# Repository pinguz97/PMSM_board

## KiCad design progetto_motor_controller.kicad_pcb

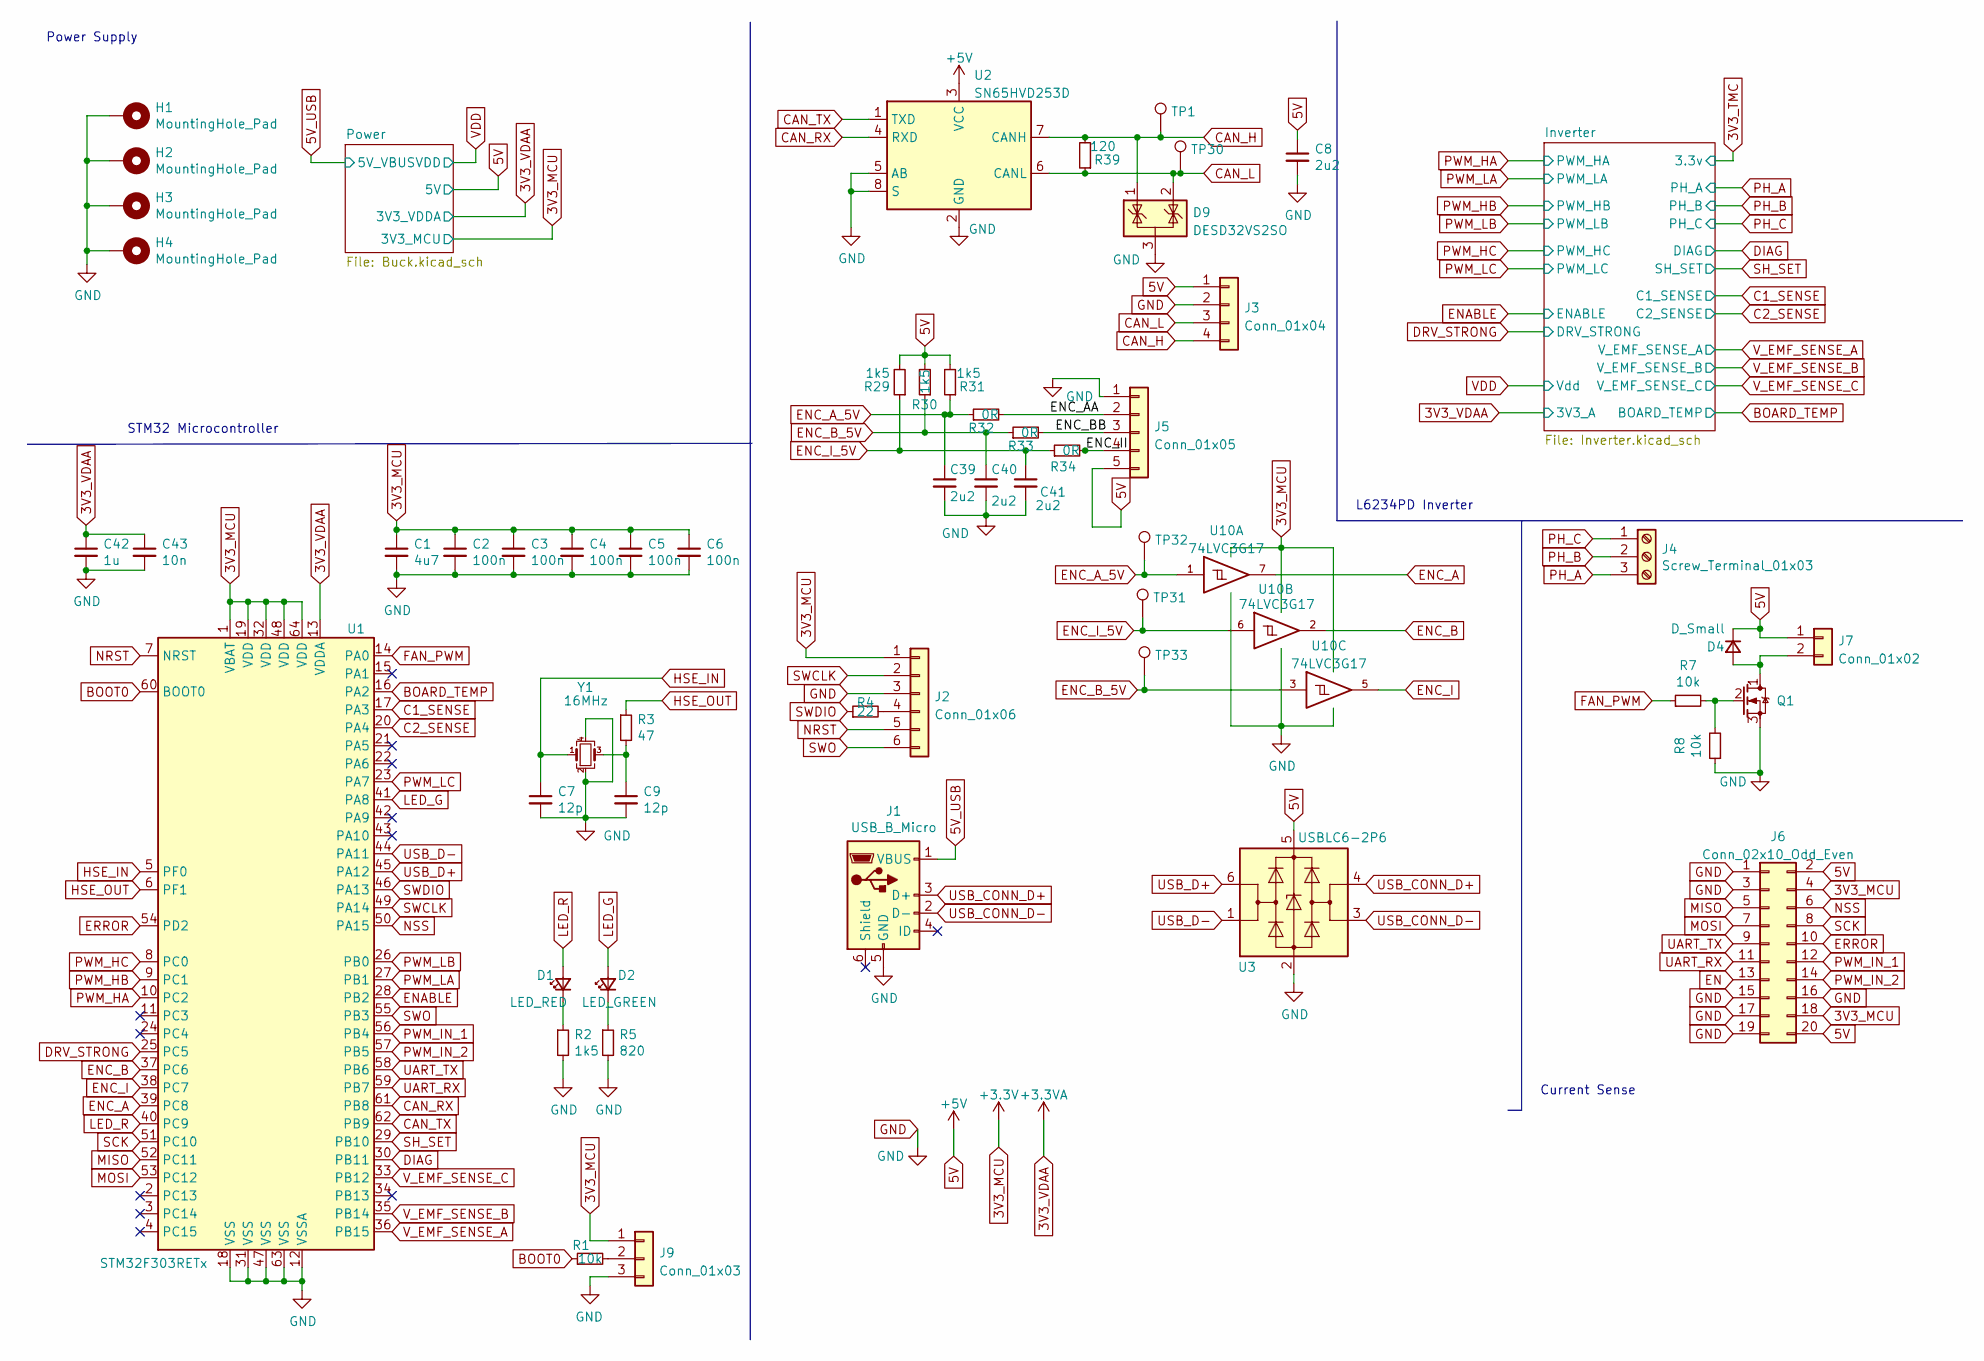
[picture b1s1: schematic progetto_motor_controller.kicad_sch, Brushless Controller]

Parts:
C1: 4u7; C_0603_1608Metric; Part CL10A475KP8NNNC
C2, C3, C4, C5, C6: 100n; C_0402_1005Metric; Part CL05B104KA5NNNC
C7, C9: 12p; C_0402_1005Metric; Part CL05C100JB5NNNC CL05C120JB5NNNC
C8, C39, C40, C41: 2u2; C_0603_1608Metric; Part CL10A225KO8NNNC
C42: 1u; C_0603_1608Metric; Part CL10B105KA8NNNC
C43: 10n; C_0402_1005Metric; Part CL05B103KB5NNNC
D1: LED_RED; LED_0603_1608Metric; Part B1931URO-20D000114U1930
D2: LED_GREEN; LED_0603_1608Metric; Part B19Y1NG--20C000113U1930
D4: D_Small; D_SOD-323; Part 1N4148WS
D9: DESD32VS2SO; SOT-23; Part DESD32VS2SO-7
H1, H2, H3, H4: MountingHole_Pad; MountingHole_3.2mm_M3_Pad_Via
J1: USB_B_Micro; USB_Micro-B_Amphenol_10118194_Horizontal
J2: Conn_01x06; JST_GH_SM06B-GHS-TB_06x1.25mm_Angled
J3: Conn_01x04; JST_GH_SM04B-GHS-TB_04x1.25mm_Angled
J4: Screw_Terminal_01x03; TerminalBlock_Phoenix_PT-1,5-3-5.0-H_1x03_P5.00mm_Horizontal
J5: Conn_01x05; JST_GH_SM05B-GHS-TB_05x1.25mm_Angled
J6: Conn_02x10_Odd_Even; JST_SHD_SM20B
J7: Conn_01x02; JST_GH_SM02B-GHS-TB_02x1.25mm_Angled
J9: Conn_01x03; PinHeader_1x03_P2.54mm_Vertical
Q1: DMG3402L-7; SOT-23; Part DMG3402L-7
R1, R7, R8: 10k; R_0603_1608Metric; Part AC0603FR-0710KL
R2, R29, R30, R31: 1k5; R_0603_1608Metric; Part AC0603JR-071K5L
R3: 47; R_0402_1005Metric
R4: 22; R_0603_1608Metric
R5: 820; R_0603_1608Metric
R32, R33, R34: 0R; R_0603_1608Metric
R39: 120; R_1210_3225Metric; Part RC1210JR-07120RL
TP1, TP30, TP31, TP32, TP33: Testpoint; TestPoint_1.0mm
U1: STM32F303RETx; LQFP-64_10x10mm_P0.5mm; Part STM32F303RETx --------
U2: SN65HVD253D; SOIC-8_3.9x4.9mm_P1.27mm; Part SN65HVD253D
U3: USBLC6-2P6; SOT-23-6; Part CM1231-02SO
U10: 74LVC3G17; VSSOP-8_2.3x2mm_P0.5mm; Part 74LVC3G34DC,125
Y1: 16MHz; Crystal_SMD_3225-4Pin_3.2x2.5mm; Part ABM8-16.000MHZ-10-1-U-T

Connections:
3V3_MCU: C1.1, C2.1, C3.1, C4.1, C5.1, C6.1, J2.1, J6.4, J6.18, J9.1, U1.1 (VBAT), U1.19 (VDD), U1.32 (VDD), U1.48 (VDD), U1.64 (VDD), U10.8 (VCC); also elsewhere on the board
3V3_VDAA: C42.1, C43.1, U1.13 (VDDA); also elsewhere on the board
5V: C8.1, D4.1 (K), J3.1, J5.5, J6.2, J6.20, J7.1, R29.2, R30.2, R31.2, U2.3 (VCC), U3.5 (VBUS); also elsewhere on the board
5V_USB: J1.1 (VBUS); also elsewhere on the board
/ENC_AA: J5.2, R32.2
/ENC_BB: J5.3, R33.2
/ENC_II: J5.4, R34.2
BOARD_TEMP: U1.16 (PA2); also elsewhere on the board
BOOT0: R1.1, U1.60 (BOOT0)
C1_SENSE: U1.17 (PA3); also elsewhere on the board
C2_SENSE: U1.20 (PA4); also elsewhere on the board
CAN_H: D9.1 (K), J3.4, R39.2, TP1.1, U2.7 (CANH)
CAN_L: D9.2 (K), J3.3, R39.1, TP30.1, U2.6 (CANL)
CAN_RX: U1.61 (PB8), U2.4 (RXD)
CAN_TX: U1.62 (PB9), U2.1 (TXD)
DIAG: U1.30 (PB11); also elsewhere on the board
DRV_STRONG: U1.25 (PC5); also elsewhere on the board
EN: J6.13
ENABLE: U1.28 (PB2); also elsewhere on the board
ENC_A: U1.39 (PC8), U10.7
ENC_A_5V: C39.1, R31.1, R32.1, TP32.1, U10.1
ENC_B: U1.37 (PC6), U10.2
ENC_B_5V: C40.1, R30.1, R33.1, TP33.1, U10.3
ENC_I: U1.38 (PC7), U10.5
ENC_I_5V: C41.1, R29.1, R34.1, TP31.1, U10.6
ERROR: J6.10, U1.54 (PD2)
FAN_PWM: R7.1, U1.14 (PA0)
GND: C1.2, C2.2, C3.2, C4.2, C5.2, C6.2, C7.2, C8.2, C9.2, C39.2, C40.2, C41.2, C42.2, C43.2, D9.3 (A), H1.1, H2.1, H3.1, H4.1, J1.5 (GND), J2.3, J3.2, J5.1, J6.1, J6.3, J6.15, J6.16, J6.17, J6.19, J9.3, Q1.3 (S), R2.2, R5.2, R8.1, U1.12 (VSSA), U1.18 (VSS), U1.31 (VSS), U1.47 (VSS), U1.63 (VSS), U2.2 (GND), U2.5 (AB), U2.8 (S), U3.2 (GND), U10.4 (GND), Y1.2, Y1.4; also elsewhere on the board
HSE_IN: C7.1, U1.5 (PF0), Y1.1
HSE_OUT: R3.1, U1.6 (PF1)
LED_G: D2.2 (A), U1.41 (PA8)
LED_R: D1.2 (A), U1.40 (PC9)
MISO: J6.5, U1.52 (PC11)
MOSI: J6.7, U1.53 (PC12)
NRST: J2.5, U1.7 (NRST)
NSS: J6.6, U1.50 (PA15)
unnamed: C9.1, R3.2, Y1.3
unnamed: D1.1 (K), R2.1
unnamed: D2.1 (K), R5.1
unnamed: D4.2 (A), J7.2, Q1.1 (D)
unnamed: J2.4, R4.2
unnamed: J9.2, R1.2
unnamed: Q1.2 (G), R7.2, R8.2
PH_A: J4.3; also elsewhere on the board
PH_B: J4.2; also elsewhere on the board
PH_C: J4.1; also elsewhere on the board
PWM_HA: U1.10 (PC2); also elsewhere on the board
PWM_HB: U1.9 (PC1); also elsewhere on the board
PWM_HC: U1.8 (PC0); also elsewhere on the board
PWM_IN_1: J6.12, U1.56 (PB4)
PWM_IN_2: J6.14, U1.57 (PB5)
PWM_LA: U1.27 (PB1); also elsewhere on the board
PWM_LB: U1.26 (PB0); also elsewhere on the board
PWM_LC: U1.23 (PA7); also elsewhere on the board
SCK: J6.8, U1.51 (PC10)
SH_SET: U1.29 (PB10); also elsewhere on the board
SWCLK: J2.2, U1.49 (PA14)
SWDIO: R4.1, U1.46 (PA13)
SWO: J2.6, U1.55 (PB3)
UART_RX: J6.11, U1.59 (PB7)
UART_TX: J6.9, U1.58 (PB6)
USB_CONN_D+: J1.3 (D+), U3.4 (I/O2)
USB_CONN_D-: J1.2 (D-), U3.3 (I/O2)
USB_D+: U1.45 (PA12), U3.6 (I/O1)
USB_D-: U1.44 (PA11), U3.1 (I/O1)
V_EMF_SENSE_A: U1.36 (PB15); also elsewhere on the board
V_EMF_SENSE_B: U1.35 (PB14); also elsewhere on the board
V_EMF_SENSE_C: U1.33 (PB12); also elsewhere on the board

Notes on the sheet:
STM32 Microcontroller
Current Sense
Power Supply
L6234PD Inverter

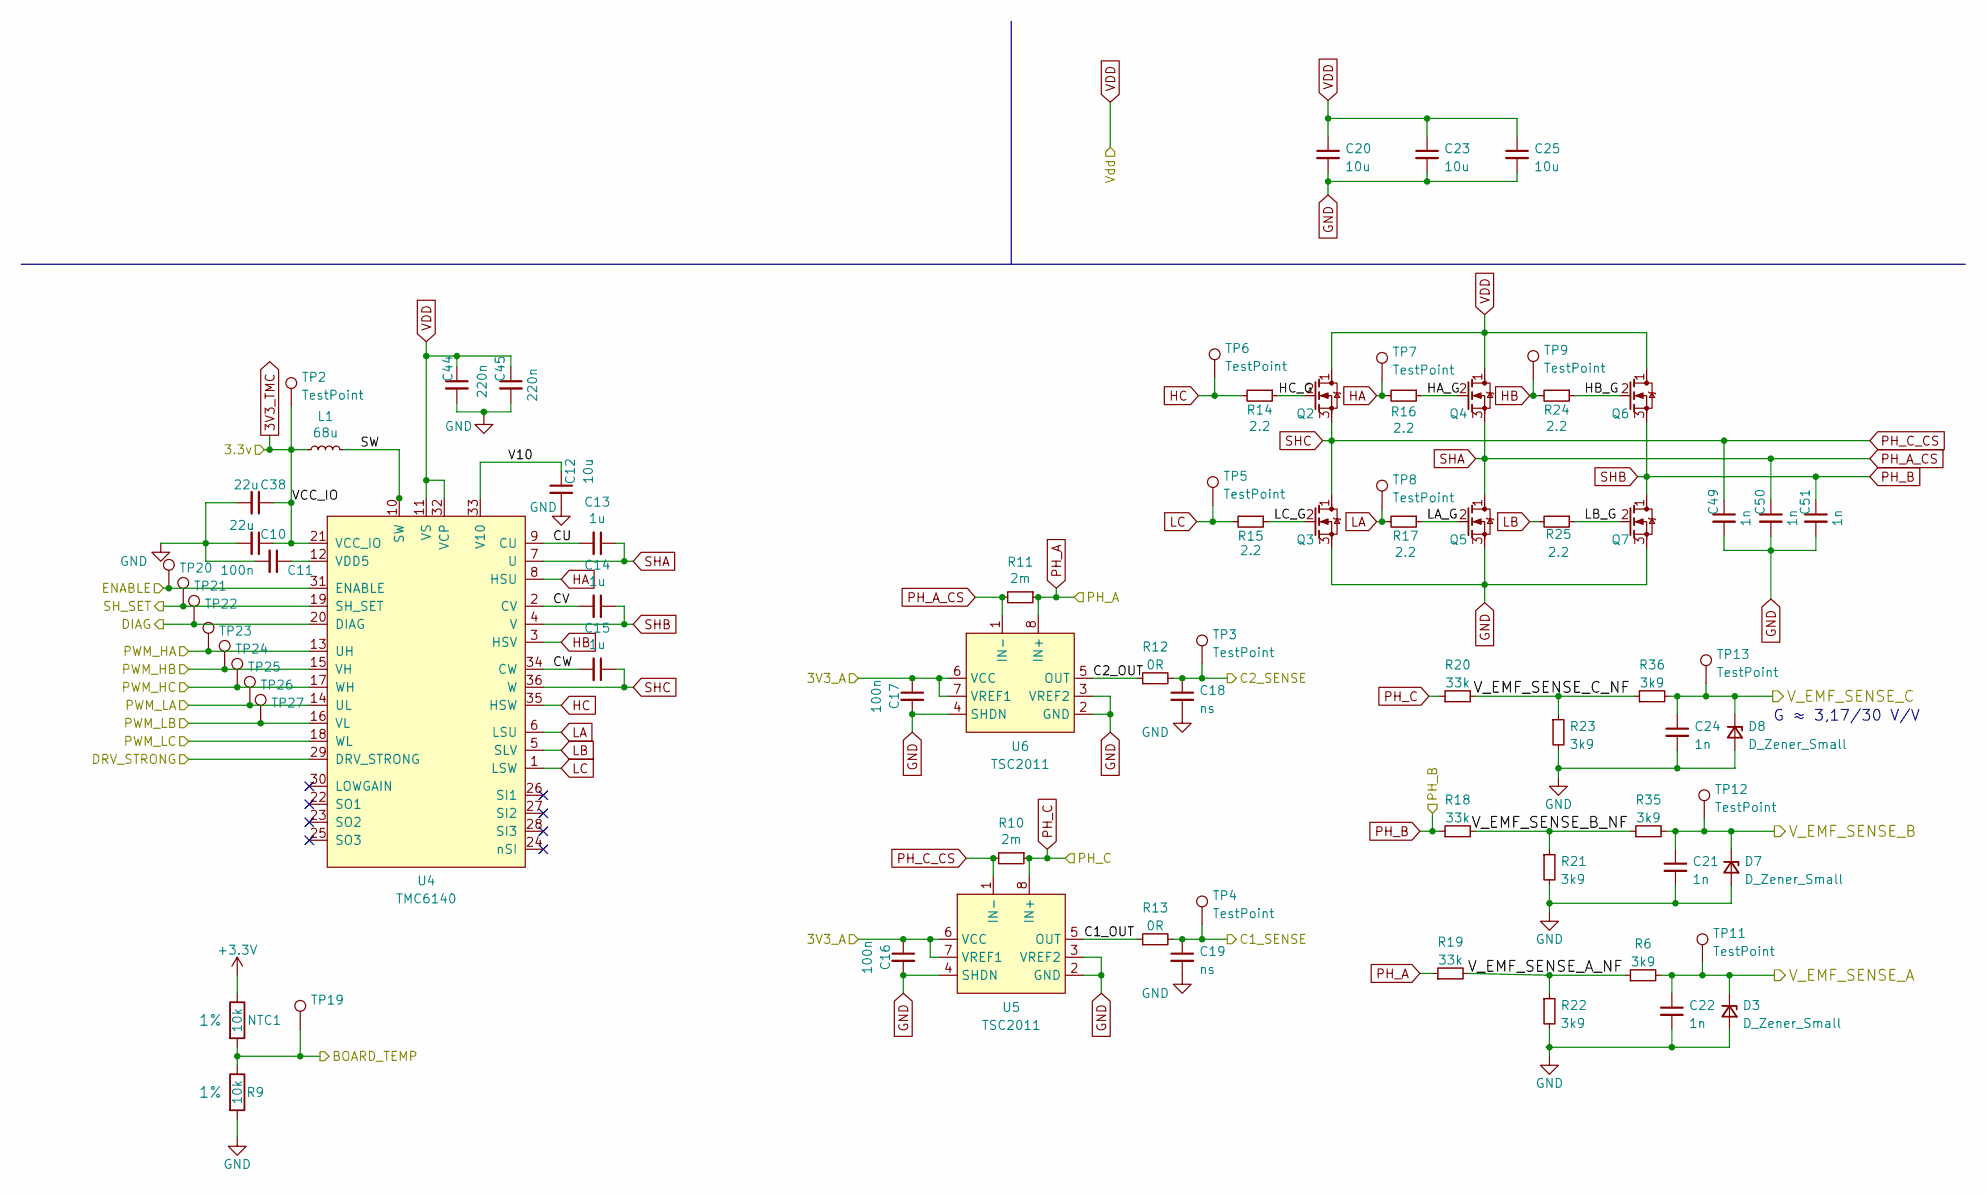
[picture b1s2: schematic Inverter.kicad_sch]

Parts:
C10, C38: 22u; C_0603_1608Metric; Part CL10A226MQ8NRNC
C11, C16, C17: 100n; C_0402_1005Metric; Part CL05B104KA5NNNC
C12: 10u; C_0603_1608Metric; Part CL21A106KOQNNNG
C13, C14, C15: 1u; C_0603_1608Metric; Part CL10B105KA8NNNC
C18, C19: ns; C_0603_1608Metric
C20, C23, C25: 10u; C_1206_3216Metric; Part CL31B106KBHNNNE
C21, C22, C24, C49, C50, C51: 1n; C_0603_1608Metric; Part CL10B102KB8NNNC
C44, C45: 220n; C_0603_1608Metric; Part CL10A224KB8NNNC
D3, D7, D8: D_Zener_Small; D_SOD-123; Part MMSZ5231B-7-F
L1: 68u; L_1210_3225Metric; Part CBC3225T680KR
NTC1: 10k; R_0603_1608Metric; Tolerance 1%; Part NCU18XH103F60RB
Q2, Q3, Q4, Q5, Q6, Q7: BSC022N04LSATMA1; TDSON-8-6_copy; Part BSC022N04LSATMA1 ------
R6, R21, R22, R23, R35, R36: 3k9; R_0603_1608Metric; Part AC0603FR-073K9L
R9: 10k; R_0603_1608Metric; Tolerance 1%; Part AC0603FR-0710KL
R10, R11: 2m; R_2512_6332Metric; Part gia prese
R12, R13: 0R; R_0603_1608Metric
R14, R15, R16, R17, R24, R25: 2.2; R_0603_1608Metric; Part AC0603FR-072R2L
R18, R19, R20: 33k; R_0603_1608Metric; Part AC0603FR-0733KL
TP2, TP3, TP4, TP5, TP6, TP7, TP8, TP9, TP11, TP12, TP13, TP19: TestPoint; TestPoint_1.0mm
TP20, TP21, TP22, TP23, TP24, TP25, TP26, TP27: Testpoint; TestPoint_1.0mm
U4: TMC6140; TMC6140-LA; Part TMC6140 ---------
U5, U6: TSC2011; SOIC-8_3.9x4.9mm_P1.27mm; Part TSC2011 ----

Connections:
3V3_MCU: NTC1.1; also elsewhere on the board
3V3_TMC: C10.1, C38.1, L1.1, TP2.1, U4.21 (VCC_IO)
3V3_VDAA: C16.1, C17.1, U5.6 (VCC), U5.7 (VREF1), U6.6 (VCC), U6.7 (VREF1); also elsewhere on the board
/Inverter/C1_OUT: R13.1, U5.5 (OUT)
/Inverter/C2_OUT: R12.1, U6.5 (OUT)
/Inverter/CU: C13.2, U4.9 (CU)
/Inverter/CV: C14.2, U4.2 (CV)
/Inverter/CW: C15.2, U4.34 (CW)
/Inverter/HA_G: Q4.2 (G), R16.1
/Inverter/HB_G: Q6.2 (G), R24.1
/Inverter/HC_G: Q2.2 (G), R14.1
/Inverter/LA_G: Q5.2 (G), R17.1
/Inverter/LB_G: Q7.2 (G), R25.1
/Inverter/LC_G: Q3.2 (G), R15.1
/Inverter/SW: L1.2, U4.10 (SW)
/Inverter/V10: C12.1, U4.33 (V10)
/Inverter/V_EMF_SENSE_A_NF: R6.1, R19.2, R22.1
/Inverter/V_EMF_SENSE_B_NF: R18.2, R21.1, R35.1
/Inverter/V_EMF_SENSE_C_NF: R20.2, R23.1, R36.1
BOARD_TEMP: NTC1.2, R9.1, TP19.1; also elsewhere on the board
C1_SENSE: C19.1, R13.2, TP4.1; also elsewhere on the board
C2_SENSE: C18.1, R12.2, TP3.1; also elsewhere on the board
DIAG: TP22.1, U4.20 (DIAG); also elsewhere on the board
DRV_STRONG: U4.29 (DRV_STRONG); also elsewhere on the board
ENABLE: TP20.1, U4.31 (ENABLE); also elsewhere on the board
GND: C10.2, C11.2, C12.2, C16.2, C17.2, C18.2, C19.2, C20.2, C21.2, C22.2, C23.2, C24.2, C25.2, C38.2, C44.2, C45.2, C49.2, C50.2, C51.2, D3.2 (A), D7.2 (A), D8.2 (A), Q3.3 (S), Q5.3 (S), Q7.3 (S), R9.2, R21.2, R22.2, R23.2, U4.37, U5.2 (GND), U5.3 (VREF2), U5.4 (SHDN), U6.2 (GND), U6.3 (VREF2), U6.4 (SHDN); also elsewhere on the board
HA: R16.2, TP7.1, U4.8 (HSU)
HB: R24.2, TP9.1, U4.3 (HSV)
HC: R14.2, TP6.1, U4.35 (HSW)
LA: R17.2, TP8.1, U4.6 (LSU)
LB: R25.2, U4.5 (SLV)
LC: R15.2, TP5.1, U4.1 (LSW)
unnamed: C11.1, U4.12 (VDD5)
PH_A: R11.1, R19.1, U6.8 (IN+); also elsewhere on the board
PH_A_CS: C13.1, C50.1, Q4.3 (S), Q5.1 (D), R11.2, U4.7 (U), U6.1 (IN-)
PH_B: C14.1, C51.1, Q6.3 (S), Q7.1 (D), R18.1, U4.4 (V); also elsewhere on the board
PH_C: R10.1, R20.1, U5.8 (IN+); also elsewhere on the board
PH_C_CS: C15.1, C49.1, Q2.3 (S), Q3.1 (D), R10.2, U4.36 (W), U5.1 (IN-)
PWM_HA: TP23.1, U4.13 (UH); also elsewhere on the board
PWM_HB: TP24.1, U4.15 (VH); also elsewhere on the board
PWM_HC: TP25.1, U4.17 (WH); also elsewhere on the board
PWM_LA: TP26.1, U4.14 (UL); also elsewhere on the board
PWM_LB: TP27.1, U4.16 (VL); also elsewhere on the board
PWM_LC: U4.18 (WL); also elsewhere on the board
SH_SET: TP21.1, U4.19 (SH_SET); also elsewhere on the board
VDD: C20.1, C23.1, C25.1, C44.1, C45.1, Q2.1 (D), Q4.1 (D), Q6.1 (D), U4.11 (VS), U4.32 (VCP); also elsewhere on the board
V_EMF_SENSE_A: C22.1, D3.1 (K), R6.2, TP11.1; also elsewhere on the board
V_EMF_SENSE_B: C21.1, D7.1 (K), R35.2, TP12.1; also elsewhere on the board
V_EMF_SENSE_C: C24.1, D8.1 (K), R36.2, TP13.1; also elsewhere on the board

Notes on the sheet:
G ≈ 3,17/30 V/V

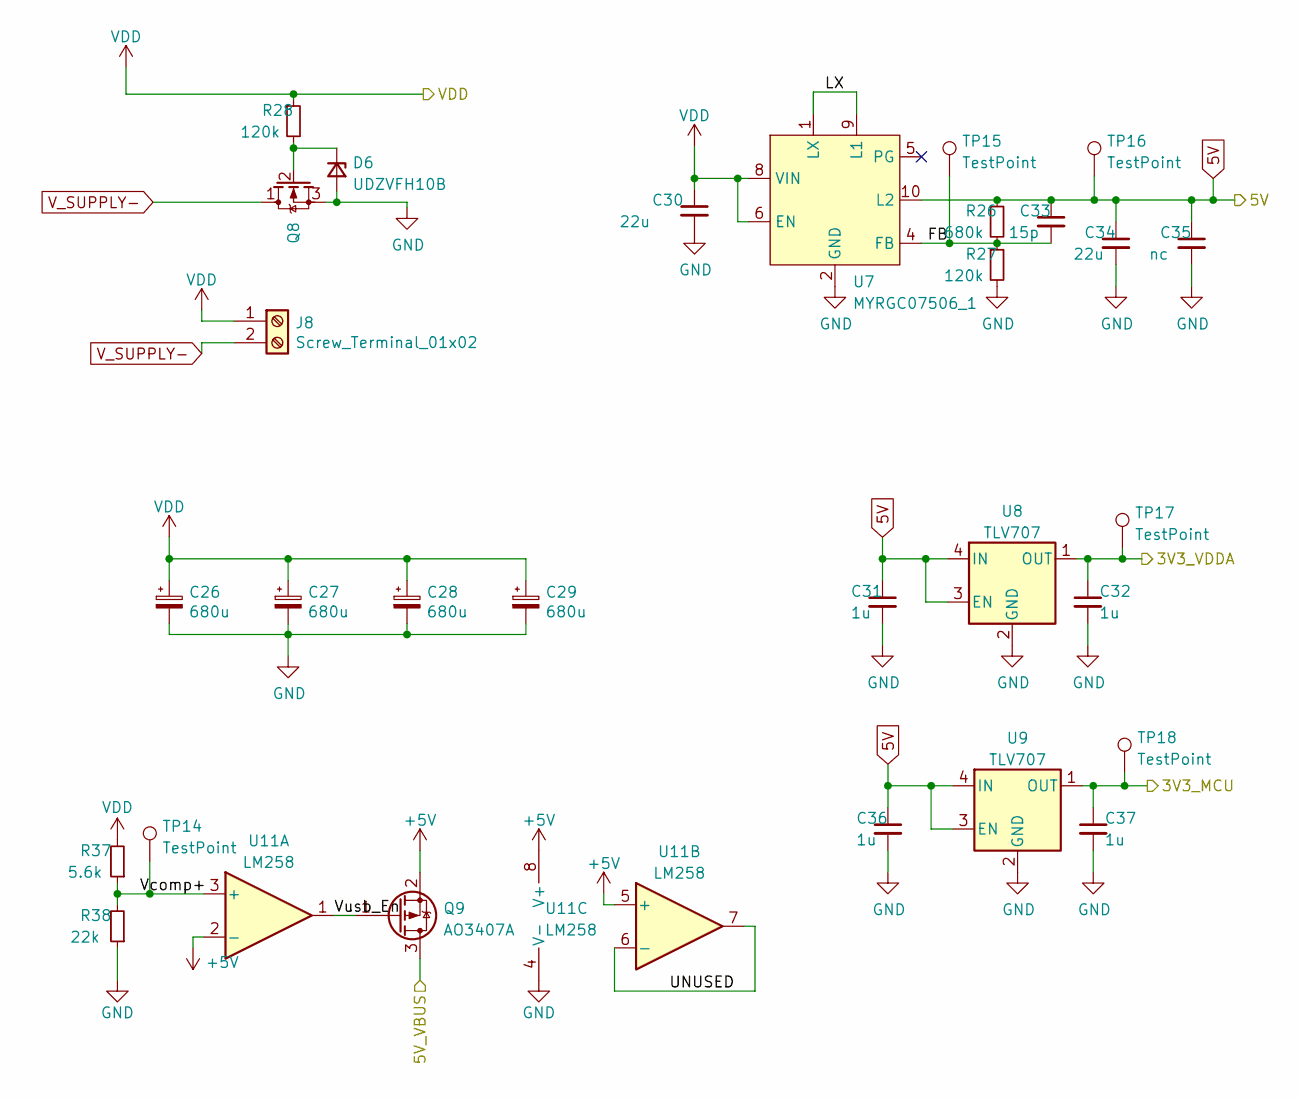
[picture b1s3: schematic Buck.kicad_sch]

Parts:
C26, C27, C28, C29: 680u; Electrolytic_Cap_12.5x13.5; Part UCZ1V471MNQ1MS
C30: 22u; C_1206_3216Metric; Part C3216X5R1V226M160AC
C31, C32, C36, C37: 1u; C_0603_1608Metric; Part CL10B105KA8NNNC
C33: 15p; C_0603_1608Metric; Part CL10C150JB8NNNC
C34: 22u; C_0603_1608Metric; Part CL10A226MQ8NRNC
C35: nc; C_0603_1608Metric
D6: UDZVFH10B; D_SOD-323_HandSoldering; Part UDZVFH10B --------
J8: Screw_Terminal_01x02; TerminalBlock_Phoenix_PT-1,5-2-3.5-H_1x02_P3.50mm_Horizontal
Q8: BSC010N04LSATMA1; TDSON-8-6_copy; Part BSC010N04LSATMA1
Q9: AO3407A; SOT-23; Part AO3407A; LCSC Part # C15127
R26: 680k; R_0603_1608Metric; Part RC0603FR-07680KL
R27, R28: 120k; R_0603_1608Metric; Part AC0603FR-07120KL
R37: 5.6k; R_0603_1608Metric; LCSC Part # C23189
R38: 22k; R_0603_1608Metric; LCSC Part # C31850
TP14, TP15, TP16, TP17, TP18: TestPoint; TestPoint_1.0mm
U7: MYRGC07506_1; Murata_picoBK; Part MYRGC07506
U8, U9: TLV707; Part TLV70733DQNT
U11: LM258; SOIC-8_3.9x4.9mm_P1.27mm; Part LM258DR; LCSC Part # C7950

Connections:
3V3_MCU: C37.1, TP18.1, U9.1 (OUT); also elsewhere on the board
3V3_VDAA: C32.1, TP17.1, U8.1 (OUT); also elsewhere on the board
5V: C31.1, C33.1, C34.1, C35.1, C36.1, Q9.2 (S), R26.1, TP16.1, U7.10 (L2), U8.3 (EN), U8.4 (IN), U9.3 (EN), U9.4 (IN), U11.2 (-), U11.5 (+), U11.8 (V+); also elsewhere on the board
5V_USB: Q9.3 (D); also elsewhere on the board
/Power/FB: C33.2, R26.2, R27.1, TP15.1, U7.4 (FB)
/Power/LX: U7.1 (LX), U7.9 (L1)
/Power/UNUSED: U11.6 (-), U11.7
/Power/Vcomp+: R37.1, R38.2, TP14.1, U11.3 (+)
/Power/Vusb_En: Q9.1 (G), U11.1
GND: C26.2, C27.2, C28.2, C29.2, C30.2, C31.2, C32.2, C34.2, C35.2, C36.2, C37.2, D6.2 (A), Q8.3 (S), R27.2, R38.1, U7.2 (GND), U7.3 (NC), U8.2 (GND), U8.5, U9.2 (GND), U9.5, U11.4 (V-); also elsewhere on the board
unnamed: D6.1 (K), Q8.2 (G), R28.2
VDD: C26.1, C27.1, C28.1, C29.1, C30.1, J8.1, R28.1, R37.2, U7.6 (EN), U7.7 (NC), U7.8 (VIN); also elsewhere on the board
V_SUPPLY-: J8.2, Q8.1 (D)

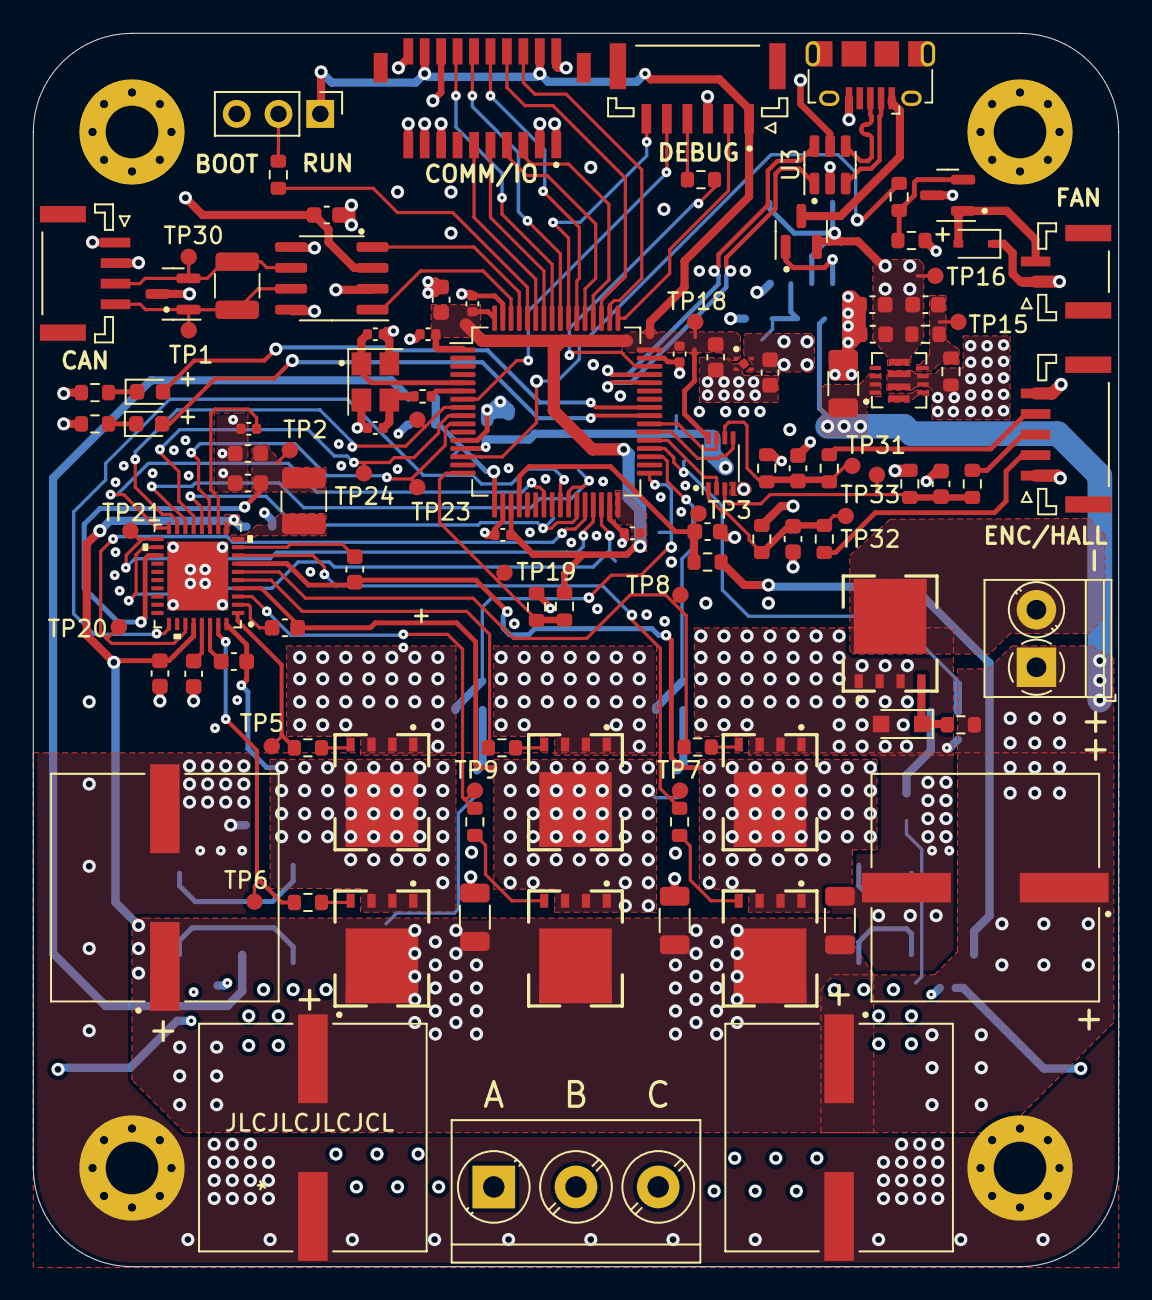
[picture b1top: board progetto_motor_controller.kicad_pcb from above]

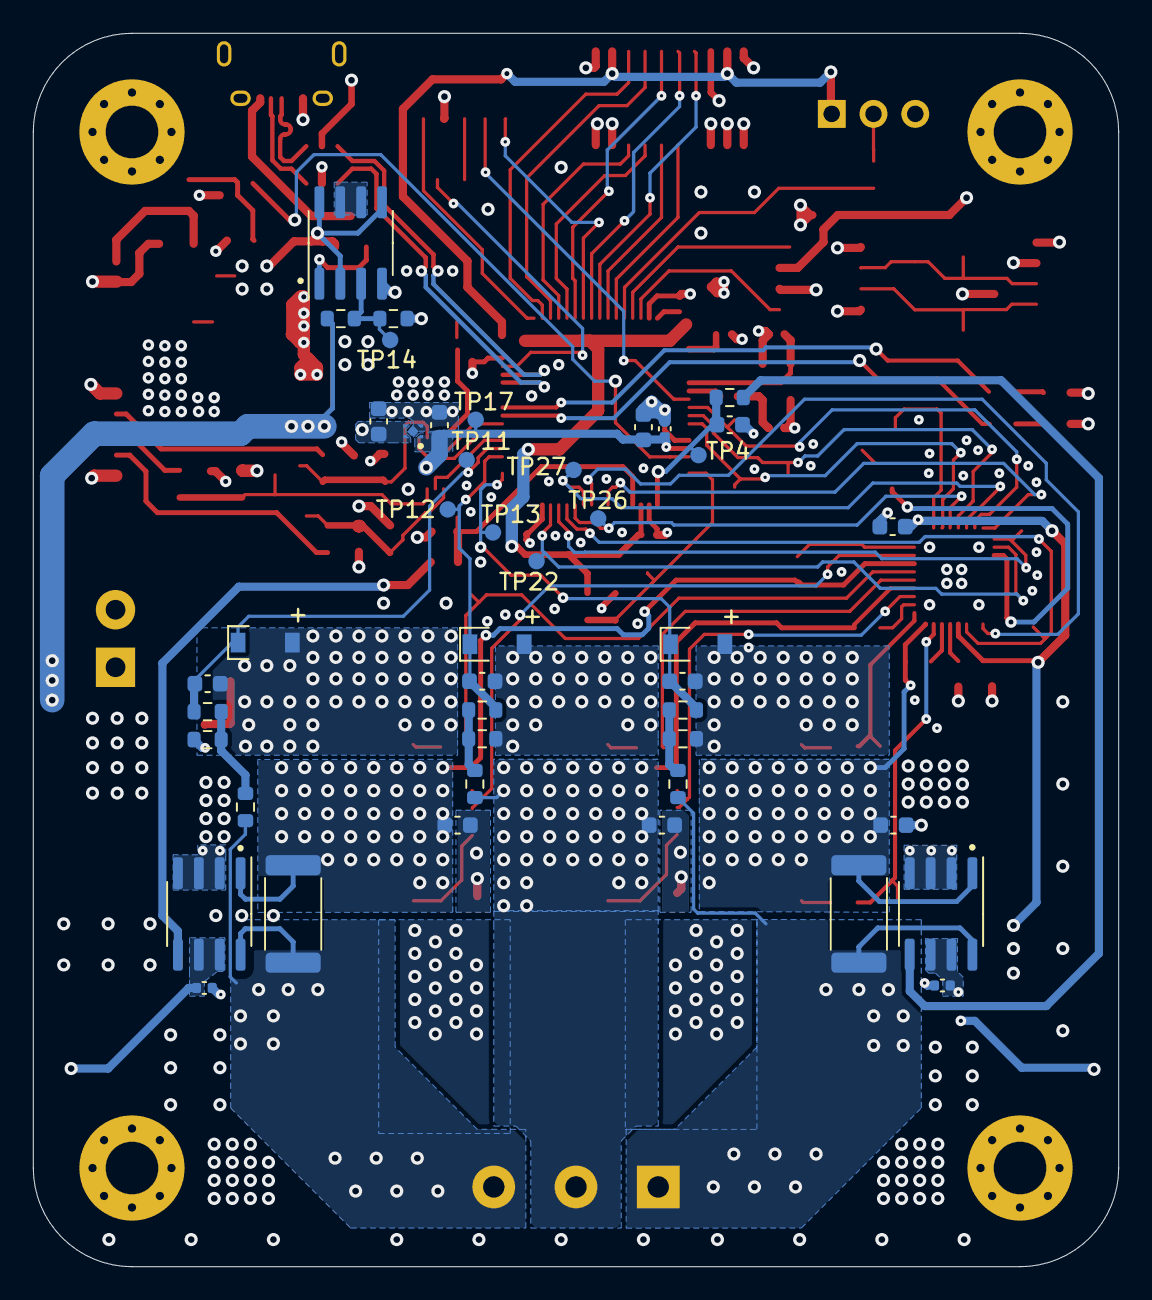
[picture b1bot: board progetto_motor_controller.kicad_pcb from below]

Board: 4 copper layers, 66.0 x 75.0 mm, 161 parts (44 on the bottom side), 101 nets.

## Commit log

2022-06-12 added local symbol library
2022-06-13 Third commit
2022-06-14 added footprints
2022-06-14 fourth commit
2022-06-15 started pcb layout
2022-06-16 added capacitor footprints
2022-06-30 rev_0.1
2022-06-30 branch test
2022-06-30 changed mosfet spacing
2022-07-01 added mosfet vias
2022-07-02 changed gate tracks layout
2022-07-04 layout
2022-07-22 before load switch
2022-07-22 buck relayout
2022-07-31 final
2022-08-12 last commit

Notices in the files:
parts and their libraries:
Copyright 2021 Accelerated Designs. All rights reserved.
